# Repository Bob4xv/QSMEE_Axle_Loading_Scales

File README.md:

This project was created for the Queensland Society of Model and Experimental Engineers (QSMEE) 
to provide a facility to measure the load presented by a locomotive axles individually.  This
enables the builders of their scale model locomotives to equalize each axle as required on both 
5" and 7 1/4" gauge track.
A facility was added to add each axle to memory giving a total weight of the locomotive.

Hardware requirements:-
Arduino uno processor, HX711 SPI Loadcell ADC, 8 character 7 segment LED I2C display module.
The load cells are two LC4103-K100 in parallel supporting a track segment.

Software requirements:-
Arduino IDE with the following libraries installed. 
	LedControl-master from git-hub.  https://github.com/wayoda/LedControl
	HX711_ADC-master from git-hub. https://github.com/olkal/HX711_ADC & https://github.com/bogde/HX711

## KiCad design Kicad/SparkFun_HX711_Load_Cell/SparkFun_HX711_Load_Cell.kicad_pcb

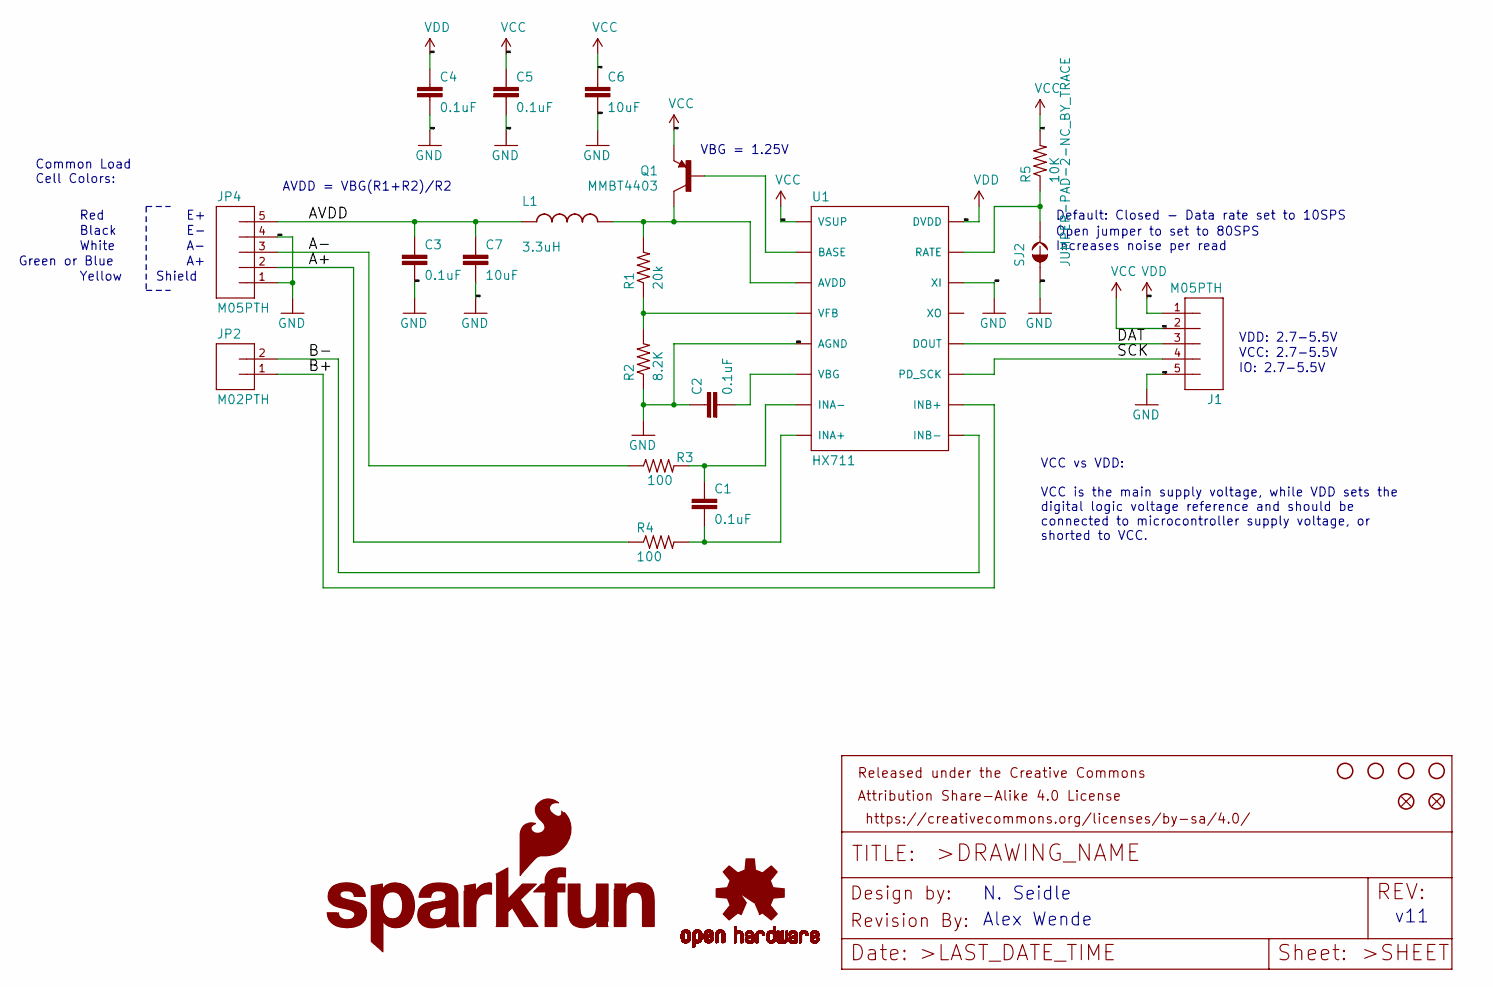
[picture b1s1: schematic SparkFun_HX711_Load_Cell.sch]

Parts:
C1, C2, C3, C4, C5: 0.1uF; 0603-CAP
C6, C7: 10uF; 1210
FID1, FID2: FIDUCIAL1X2; FIDUCIAL-1X2
FRAME1: FRAME-LETTER; CREATIVE_COMMONS
J1: M05PTH; 1X05
JP2: M02PTH; 1X02
JP4: M05PTH; 1X05
L1: 3.3uH; 0805
LOGO1: SFE_LOGO_NAME_FLAME.1_INCH; SFE_LOGO_NAME_FLAME_.1
Q1: MMBT4403; SOT23-3
R1: 20k; 0603-RES
R2: 8.2K; 0603-RES
R3, R4: 100; 0603-RES
R5: 10K; 0603-RES
SJ2: JUMPER-PAD-2-NC_BY_TRACE; PAD-JUMPER-2-NC_BY_TRACE_YES_SILK
STANDOFF1, STANDOFF2, STANDOFF3, STANDOFF4: STAND-OFF
U1: HX711; SO16
U7: OSHW-LOGOS; OSHW-LOGO-S
U$1: REVISION

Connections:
/A+: JP4.2, R4.1
/A-: JP4.3, R3.1
/AVDD: C3.1, C7.1, JP4.5, L1.1
/B+: JP2.1, U1.10 (INB+)
/B-: JP2.2, U1.9 (INB-)
/DAT: J1.3, U1.12 (DOUT)
/SCK: J1.4, U1.11 (PD_SCK)
GND: C2.1, C3.2, C4.2, C5.2, C6.2, C7.2, J1.5, JP4.1, JP4.4, R2.1, SJ2.1, U1.5 (AGND), U1.14 (XI)
unnamed: C1.1, R3.2, U1.7 (INA-)
unnamed: C1.2, R4.2, U1.8 (INA+)
unnamed: C2.2, U1.6 (VBG)
unnamed: L1.2, Q1.3 (C), R1.2, U1.3 (AVDD)
unnamed: Q1.1 (B), U1.2 (BASE)
unnamed: R1.1, R2.2, U1.4 (VFB)
unnamed: R5.1, SJ2.2, U1.15 (RATE)
VCC: C5.1, C6.1, J1.2, Q1.2 (E), R5.2, U1.1 (VSUP)
VDD: C4.1, J1.1, U1.16 (DVDD)

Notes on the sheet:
VCC: 2.7-5.5V
VBG = 1.25V
AVDD = VBG(R1+R2)/R2
Default: Closed - Data rate set to 10SPS
Open jumper to set to 80SPS Increases noise per read
IO: 2.7-5.5V
Shield
VDD: 2.7-5.5V
VCC vs VDD: VCC is the main supply voltage, while VDD sets the digital logic voltage reference and should be connected to microcontroller supply voltage, or shorted to VCC.
Alex Wende
N. Seidle
v11
Yellow
Common Load Cell Colors:
Green or Blue
White
Black
Red

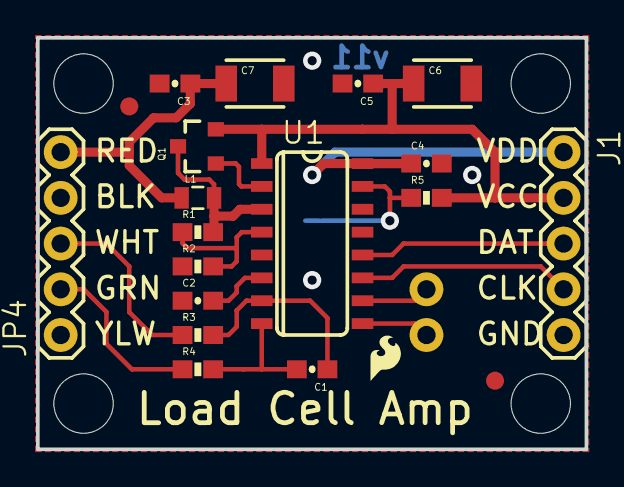
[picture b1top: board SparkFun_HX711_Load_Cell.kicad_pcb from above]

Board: 2 copper layers, 30.5 x 22.9 mm, 30 parts (0 on the bottom side), 17 nets.

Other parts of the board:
LOGO3: SFE_LOGO_FLAME.1_INCH; SFE_LOGO_FLAME_.1

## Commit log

2019-11-12 Fix symlink on .ino and update README
2019-11-13 Tidy up schematic and add PDF
2020-02-13 Update user doc with construct details and add pdf of this file

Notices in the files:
parts and their libraries:
https://creativecommons.org/licenses/by-sa/4.0
Released under the Creative Commons Attribution Share-Alike 4.0 License
